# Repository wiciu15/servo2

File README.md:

# Servo 2
## 3-phase AC servomotor driver

This is a project of a servo inverter to drive 3-phase AC motor with/out encoder feedback

It's in alpha development so there are many bugs and things included in software but not really working/tested.

DEMO video: https://www.youtube.com/watch?v=Hu02lt5aCbM

CNC DEMO: https://www.youtube.com/watch?v=LXm4no8DIPE

This is a free software under the GNU license, you can redistribute it and/or modify it under the terms
of the GNU General Public License version 3 as published by the Free Software Foundation.
This project is shared with public for educational purposes, without WARRANTY and Author is not liable for any damages caused directly
or indirectly by this software/hardware. The board is mains-powered. High voltage can kill you. Have caution when using high voltage devices

## Features

- Manual voltage and frequency control
- U/f scalar motor control
- Open loop current control for test purposes
- Field-oriented vector control (FOC) for PMSM/BLDC motors with encoder feedback
- Encoders support:
  -  ABZ encoder with differential driver output, needs one manual rotation to index with a rotor properly
  -  Mitsubishi J2/J2s/J4/JE series, baud rate 2 500 000 bits/s, implementation is working but need some polish
  -  Tamagawa T-Format encoders - tested with ABB BSM-series motor, baud rate 2 500 000 bits/s, most robust implementation and testing at this moment
  -  Panasonic minas series encoder - support in early development, not much tested and buggy
  -  DELTA NH4 series T+ T- encoder - very early development
- Braking chopper control
- under/overvoltage, overcurrent, short-circuit and other errors detection and handling
- Communication with PC using MODBUS over USB-CDC
- simple CANopen node for fieldbus control
- Parameter set, with non-volatile storage in external EEPROM
- control and monitoring of drive using OLED screen and buttons
- ramp generators and limiters for current,speed and position control loops

## To-do in the future

- I2t thermal monitoring of motor
- sensorless rotor angle aquisition
- analog and digital I/O
- step/dir input
- current and speed loop gains auto-tuning
- motor parameters automatic measurement

## Used third-party software
- I2C EEPROM driver by ControllersTech
- OLED driver https://github.com/afiskon/stm32-ssd1306
- stModbus https://github.com/wiciu15/stModbus/
- CANopenNode https://github.com/CANopenNode/CANopenNode
- embedded printf implementation https://github.com/mpaland/printf
- FreeRTOS

## Hardware modification
MOdifications of rev.A of CPU board
- data/command line to OLED screen(PA15)
- bridge between tim1break input (PE15) and overcurrent interrupt(PA1)(break interrupt was not working i dont know why just bridged it to EXTI on other pin).
- OLED CLK is moved to PA5, PB3 is used as DEBUG_SWO.
- added filter to GND on FAULT line from power board to enchance noise rejection from EMI(i was getting random short-circuit errors).

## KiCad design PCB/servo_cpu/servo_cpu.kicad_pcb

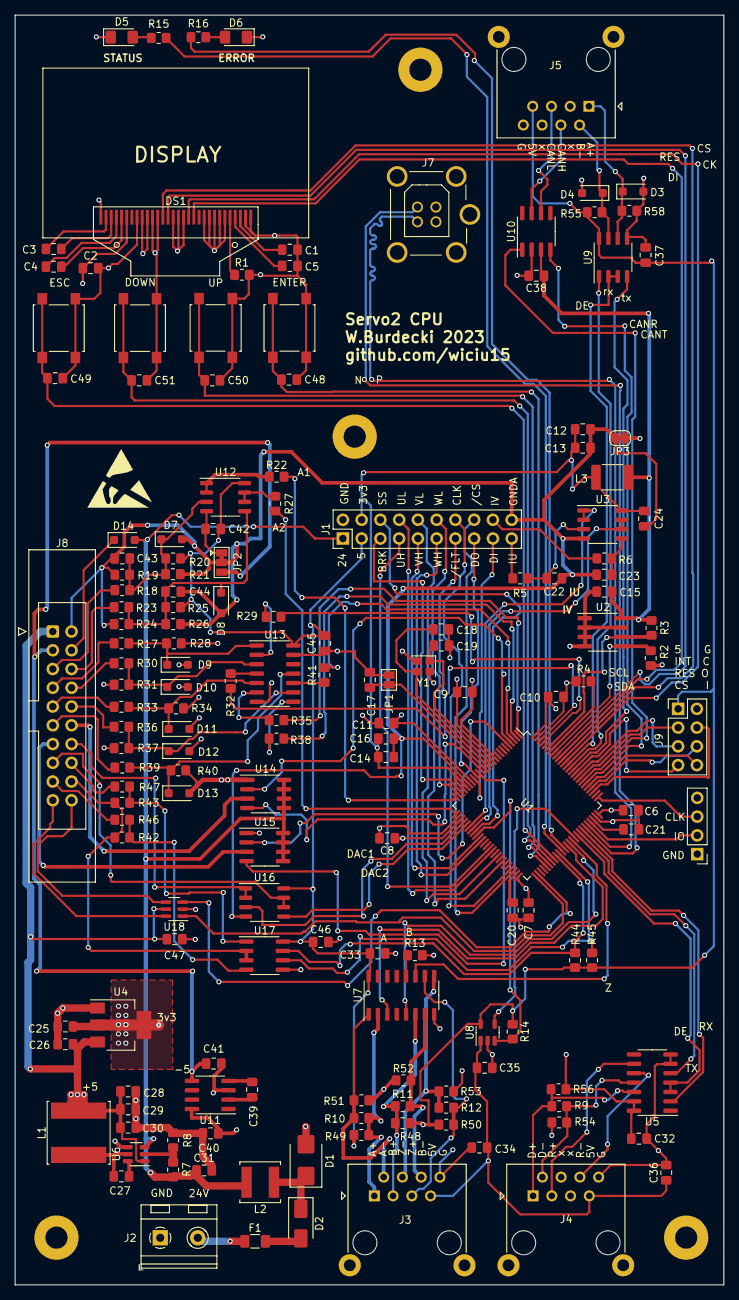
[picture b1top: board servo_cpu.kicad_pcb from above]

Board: 4 copper layers, 96.0 x 172.0 mm, 166 parts (0 on the bottom side), 151 nets.

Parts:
C1, C2, C3, C4, C5, C6, C7, C8, C9, C10, C11, C12, C13, C14, C15, C16, C20, C21, C24, C25, C26, C32, C33, C34, C35, C36, C37, C38, C40: 2u2; C_0805_2012Metric_Pad1.18x1.45mm_HandSolder
C17, C27, C42, C43, C44, C45, C46, C47, C48, C49, C50, C51: 100n; C_0805_2012Metric_Pad1.18x1.45mm_HandSolder
C18, C19: 12p; C_0805_2012Metric_Pad1.18x1.45mm_HandSolder
C22, C23: 1u; C_0805_2012Metric_Pad1.18x1.45mm_HandSolder
C28, C29, C30, C31, C39, C41: 22u; C_0805_2012Metric_Pad1.18x1.45mm_HandSolder
D1: SM6T27A; D_SMB
D2: US1B; D_SMA
D3, D4: BZT52B6v2; D_SOD-123F
D5: GREEN_LED; D_1206_3216Metric_Pad1.42x1.75mm_HandSolder
D6: RED_LED; D_1206_3216Metric_Pad1.42x1.75mm_HandSolder
D7, D8, D9, D10, D11, D12, D13: BZT52B5v1; D_SOD-123F
D14: 1N4148; D_SOD-123F
DS1: OLED-128O064D
F1: 615mA PTC; Fuse_1206_3216Metric
J1: PWR board; PinHeader_2x10_P2.54mm_Vertical
J2: Control power; TerminalBlock_RND_205-00232_1x02_P5.08mm_Horizontal
J3: ABZ; RJ45_Ninigi_GE
J4: Serial Encoder; RJ45_Ninigi_GE
J5: CONN; RJ45_Ninigi_GE
J6: DEBUG; PinHeader_1x04_P2.54mm_Vertical
J7: USB_B; USB
J8: I/O; IDC-Header_2x10_P2.54mm_Latch_Vertical
J9: EXT; PinHeader_2x04_P2.54mm_Vertical
JP1: RESET; SolderJumper-2_P1.3mm_Open_Pad1.0x1.5mm
JP2: OPA-V; SolderJumper-3_P1.3mm_Bridged12_Pad1.0x1.5mm
JP3: GND; SolderJumper-2_P1.3mm_Bridged_RoundedPad1.0x1.5mm
L1: 4u7; L_Sunlord_SWPA8040S
L2: 10u; L_Sunlord_SWPA5040S
L3: 470u; L_1812_4532Metric_Pad1.30x3.40mm_HandSolder
MH1, MH1#2, MH1#3, MH1#4: MountingHole_2.7mm_M2.5_DIN965_Pad
R1: 820k; R_0805_2012Metric_Pad1.20x1.40mm_HandSolder
R2, R3: 4,7k; R_0805_2012Metric_Pad1.20x1.40mm_HandSolder
R4, R15, R16, R44, R45, R55: 1k; R_0805_2012Metric_Pad1.20x1.40mm_HandSolder
R5, R6: 22R; R_0805_2012Metric_Pad1.20x1.40mm_HandSolder
R7: 220k; R_0805_2012Metric_Pad1.20x1.40mm_HandSolder
R8: 18k; R_0805_2012Metric_Pad1.20x1.40mm_HandSolder
R9, R22, R27: 150R; R_0805_2012Metric_Pad1.20x1.40mm_HandSolder
R10, R11, R12: 220R; R_0805_2012Metric_Pad1.20x1.40mm_HandSolder
R13, R14, R17, R18, R19, R23, R24, R29, R30, R32, R33, R35, R36, R38, R39, R41: 10k; R_0805_2012Metric_Pad1.20x1.40mm_HandSolder
R20, R21, R25, R26: 3k3; R_0805_2012Metric_Pad1.20x1.40mm_HandSolder
R28, R31, R34, R37, R40, R42, R43: 2k2; R_0805_2012Metric_Pad1.20x1.40mm_HandSolder
R46, R47, R48, R49, R50, R51, R52, R53, R54, R56, R58: 470R; R_0805_2012Metric_Pad1.20x1.40mm_HandSolder
SW1: ENTER; SW_SPST_B3S-1000
SW2: ESC; SW_SPST_B3S-1000
SW3: UP; SW_SPST_B3S-1000
SW4: DOWN; SW_SPST_B3S-1000
U1: STM32F407VETx; LQFP-100_14x14mm_P0.5mm
U2: M24C02-WMN; SOIC-8_3.9x4.9mm_P1.27mm
U3, U12, U16: TS912; SO-8_3.9x4.9mm_P1.27mm
U4: AP1117-33; SOT-223-3_TabPin2
U5: ISL83491; SO-14_3.9x8.65mm_P1.27mm
U6: AP63205WU; TSOT-23-6
U7: AM26LS32A; SO-16_3.9x9.9mm_P1.27mm
U8: AP2151A; SOT-23-5
U9: MAX485E; SO-8_3.9x4.9mm_P1.27mm
U10: SN65HVD232; SOIC-8_3.9x4.9mm_P1.27mm
U11: LMC7660; SOIC-8_3.9x4.9mm_P1.27mm
U13: 74HC14; SO-14_3.9x8.65mm_P1.27mm
U14, U15: ISP742RI; SOIC-8_3.9x4.9mm_P1.27mm
U17: VO0661T; SOIC-8_3.9x4.9mm_P1.27mm
U18: 74LVC2G04; SC-74-6_1.5x2.9mm_P0.95mm
Y1: 16M xt224; Crystal_SMD_2520-4Pin_2.5x2.0mm

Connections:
+3.3VA: C12.1, C13.1, C14.1, C16.1, C24.1, J1.19, L3.1, U1.21 (VREF+), U1.22 (VDDA), U3.8 (V+)
+3V3: C2.1, C6.1, C7.1, C8.1, C9.1, C10.1, C11.1, C15.1, C25.1, C32.1, C38.1, DS1.6 (VBAT), DS1.9 (VDD), DS1.10 (BS0), J6.4, L3.2, R2.1, R3.1, R56.1, U1.11 (VDD), U1.19 (VDD), U1.28 (VDD), U1.50 (VDD), U1.75 (VDD), U1.100 (VDD), U2.8 (VCC), U4.2 (VO), U5.13 (VCC), U5.14 (VCC), U10.3 (VCC)
+5V: C26.1, C28.1, C29.1, C30.1, C33.1, C37.1, C40.1, C42.1, C45.1, C46.1, C47.1, J1.2, J5.7, J8.1, J9.1, L1.2, R14.1, R20.2, R25.2, R44.2, R45.2, R48.1, R49.1, R50.1, R55.1, U4.3 (VI), U6.1 (FB), U7.16 (Vcc), U8.5 (IN), U9.8 (VCC), U11.8 (V+), U12.8 (V+), U13.14 (VCC), U16.8 (V+), U17.8 (VCC), U18.5 (VCC)
+5VL: C34.1, C35.1, C36.1, J3.7, J4.7, U8.1 (OUT)
+24V: C31.1, D14.2 (A), J1.1, L2.2, R7.1, U6.3 (IN), U14.5 (Vbb), U14.6 (Vbb), U14.7 (Vbb), U14.8 (Vbb), U15.5 (Vbb), U15.6 (Vbb), U15.7 (Vbb), U15.8 (Vbb)
-5V: C41.1, J8.3, JP2.3 (B), U11.5 (VOUT)
A: J3.1, R10.2, R49.2, U7.2 (1A)
A+: D3.1 (K), J5.1, R58.1, U9.6 (A)
ADC_CLK: J1.14, U1.47 (PB10)
ADC_CS: J1.13, U1.48 (PB11)
ADC_MISO: J1.8, U1.17 (PC2)
ADC_MOSI: J1.9, U1.18 (PC3)
AIN1: J8.5, R18.2
AIN1_ADC: R22.1, U1.25 (PA2)
AIN2: J8.6, R23.2
AIN2_ADC: R27.1, U1.26 (PA3)
AOUT1: J8.14, U16.1, U16.2 (-)
AOUT2: J8.15, U16.6 (-), U16.7
A_OUT: J8.19, U18.6
B: J3.3, R11.1, R48.2, U7.6 (2A)
B-: D4.1 (K), J5.2, R55.2, U9.7 (B)
BRAKE: J1.3, U1.23 (PA0)
BTN_DOWN: C51.1, SW4.1, U1.57 (PD10)
BTN_ENTER: C48.1, SW1.1, U1.55 (PD8)
BTN_ESC: C49.1, SW2.1, U1.58 (PD11)
BTN_UP: C50.1, SW3.1, U1.56 (PD9)
B_OUT: J8.20, U18.4
CANH: J5.4, U10.7 (CANH)
CANL: J5.5, U10.6 (CANL)
CAN_RX: U1.81 (PD0), U10.4 (R)
CAN_TX: U1.82 (PD1), U10.1 (D)
DAC1: U1.29 (PA4), U16.3 (+)
DAC2: U1.30 (PA5), U16.5 (+)
DEBUG_CLK: J6.3, U1.76 (PA14)
DEBUG_IO: J6.2, U1.72 (PA13)
DIN1: J8.7, R17.2
DIN1_CPU: R29.2, U1.97 (PE0)
DIN2: J8.8, R30.2
DIN2_CPU: R32.2, U1.98 (PE1)
DIN3: J8.9, R33.2
DIN3_CPU: R35.2, U1.1 (PE2)
DIN4: J8.10, R36.2
DIN4_CPU: R38.2, U1.2 (PE3)
DIN5: J8.11, R39.2
DIN5_CPU: R41.2, U1.3 (PE4)
DISPLAY_CLK: DS1.18 (D0), U1.89 (PB3)
DISPLAY_MOSI: DS1.19 (D1), U1.91 (PB5)
DOUT1: J8.12, U14.3 (OUT)
DOUT1_CPU: U1.4 (PE5), U14.2 (IN)
DOUT1_STATUS: U1.15 (PC0), U14.4 (ST)
DOUT2: J8.13, U15.3 (OUT)
DOUT2_CPU: U1.5 (PE6), U15.2 (IN)
DOUT2_STATUS: U1.16 (PC1), U15.4 (ST)
EEPROM_SCL: R3.2, U1.95 (PB8), U2.6 (SCL)
EEPROM_SDA: R2.2, U1.93 (PB7), U2.5 (SDA)
ENCODER_DE: U1.67 (PA8), U5.3 (~RE), U5.4 (DE)
ENCODER_ENABLE: U1.66 (PC9), U8.4 (EN)
ENCODER_RX: U1.69 (PA10), U5.2 (RO)
ENCODER_TX: U1.68 (PA9), U5.5 (DI)
ENC_A: U1.63 (PC6), U7.3 (1Y)
ENC_A_OUT_CPU: U1.51 (PB12), U18.1
ENC_B: U1.64 (PC7), U7.5 (2Y)
ENC_B_OUT_CPU: U1.52 (PB13), U18.3
ENC_Z: U1.65 (PC8), U7.11 (3Y)
EXT_CLK: J9.4, U1.78 (PC10)
EXT_CS: J9.7, U1.85 (PD4)
EXT_INT: J9.3, U1.83 (PD2)
EXT_MISO: J9.6, U1.79 (PC11)
EXT_MOSI: J9.8, U1.80 (PC12)
EXT_RESET: J9.5, U1.84 (PD3)
GND: C1.2, C2.2, C5.2, C6.2, C7.2, C8.2, C9.2, C10.2, C11.2, C15.2, C17.2, C18.2, C19.2, C20.2, C21.2, C25.2, C26.2, C28.2, C29.2, C30.2, C31.2, C32.2, C33.2, C34.2, C35.2, C36.2, C37.2, C38.2, C40.2, C41.2, C45.2, C46.2, C47.2, C48.2, C49.2, C50.2, C51.2, D1.2 (A2), D3.2 (A), D4.2 (A), D5.1 (K), D6.1 (K), D9.2 (A), D10.2 (A), D11.2 (A), D12.2 (A), D13.2 (A), DS1.1 (GND), DS1.8 (VSS), DS1.11 (BS1), DS1.12 (BS2), DS1.15 (D/~C), DS1.16 (R/~W), DS1.17 (E/~RD), DS1.21 (D3), DS1.22 (D4), DS1.23 (D5), DS1.24 (D6), DS1.25 (D7), DS1.29 (VLSS), DS1.30 (GND), J1.20, J2.1, J3.8, J3.SH, J4.8, J4.SH, J5.8, J5.SH, J6.1, J7.4 (GND), J7.5 (Shield), J9.2, JP1.1 (A), JP3.1 (A), MH1.1, MH1#2.1, MH1#3.1, MH1#4.1, R1.2, R4.1, R8.2, R13.2, R28.1, R31.1, R34.1, R37.1, R40.1, R51.2, R52.2, R53.2, R54.2, R58.2, SW1.2, SW2.2, SW3.2, SW4.2, U1.10 (VSS), U1.27 (VSS), U1.74 (VSS), U1.99 (VSS), U2.1 (E0), U2.2 (E1), U2.3 (E2), U2.4 (VSS), U2.7 (~WC), U4.1 (GND), U5.6 (GND), U5.7 (GND), U6.4 (GND), U7.8 (GND), U8.2 (GND), U9.5 (GND), U10.2 (GND), U11.3 (GND), U13.7 (GND), U13.13, U14.1 (GND), U15.1 (GND), U17.5 (GND), U18.2 (GND), Y1.2, Y1.4
GNDA: C12.2, C13.2, C14.2, C16.2, C22.2, C23.2, C24.2, C43.2, C44.2, D7.2 (A), D8.2 (A), J1.11, J8.2, JP2.2 (C), JP3.2 (B), R19.1, R21.1, R24.1, R26.1, U1.20 (VSSA), U3.4 (V-), U16.4 (V-)
IGBT_fault: J1.7, U1.24 (PA1)
I_U: J1.10, R5.2
I_V: J1.12, R6.2
LED_ERROR: R16.1, U1.62 (PD15)
LED_STATUS: R15.1, U1.61 (PD14)
MD: J4.1, R9.1, R56.2, U5.12 (A)
MDR: J4.2, R9.2, R54.1, U5.11 (~B)
MODBUS_DE: U1.88 (PD7), U9.2 (~RE), U9.3 (DE)
MODBUS_RX: U1.87 (PD6), U9.1 (RO)
MODBUS_TX: U1.86 (PD5), U9.4 (DI)
MR: J4.3, U5.9 (Y)
MRR: J4.6, U5.10 (~Z)
unnamed: D1.1 (A1), D2.1 (K), L2.1
unnamed: D2.2 (A), F1.2
unnamed: D5.2 (A), R15.2
unnamed: D6.2 (A), R16.2
unnamed: C43.1, D7.1 (K), R18.1, R19.2, R20.1, R21.2, U12.3 (+)
unnamed: C44.1, D8.1 (K), R23.1, R24.2, R25.1, R26.2, U12.5 (+)
unnamed: D9.1 (K), R17.1, R28.2, U13.1
unnamed: D10.1 (K), R30.1, R31.2, U13.3
unnamed: D11.1 (K), R33.1, R34.2, U13.5
unnamed: D12.1 (K), R36.1, R37.2, U13.9
unnamed: D13.1 (K), R39.1, R40.2, U13.11
unnamed: D14.1 (K), J8.4
unnamed: C4.2, DS1.5 (C1N)
unnamed: C4.1, DS1.4 (C1P)
unnamed: C3.1, DS1.2 (C2N)
unnamed: C3.2, DS1.3 (C2P)
unnamed: DS1.26 (IREF), R1.1
unnamed: C1.1, DS1.28 (VCC)
unnamed: C5.1, DS1.27 (VCOMH)
unnamed: F1.1, J2.2
unnamed: C17.1, JP1.2 (B), U1.14 (NRST)
unnamed: C42.2, JP2.1 (A), U12.4 (V-)
unnamed: R29.1, U13.2
unnamed: R32.1, U13.4
unnamed: R35.1, U13.6
unnamed: R38.1, U13.8
unnamed: R41.1, U13.10
unnamed: R4.2, U1.94 (BOOT0)
unnamed: U1.31 (PA6), U3.1, U3.2 (-)
unnamed: U1.32 (PA7), U3.6 (-), U3.7
unnamed: C19.1, U1.12 (PH0), Y1.1
unnamed: C18.1, U1.13 (PH1), Y1.3
unnamed: C20.1, U1.49 (VCAP_1)
unnamed: C21.1, U1.73 (VCAP_2)
unnamed: C22.1, R5.1, U3.3 (+)
unnamed: C23.1, R6.1, U3.5 (+)
unnamed: C27.2, U6.6 (BST)
unnamed: R7.2, R8.1, U6.2 (EN)
unnamed: C27.1, L1.1, U6.5 (SW)
unnamed: R13.1, U7.12 (/G)
unnamed: C39.1, U11.2 (CAP+)
unnamed: C39.2, U11.4 (CAP-)
unnamed: R22.2, U12.1, U12.2 (-)
unnamed: R27.2, U12.6 (-), U12.7
unnamed: R43.2, R47.2, U17.1 (A1)
unnamed: R42.1, R46.2, U17.4 (A2)
PWMU_H: J1.4, U1.39 (PE8)
PWMU_L: J1.17, U1.40 (PE9)
PWMV_H: J1.5, U1.35 (PB0)
PWMV_L: J1.16, U1.42 (PE11)
PWMW_H: J1.6, U1.36 (PB1)
PWMW_L: J1.15, U1.44 (PE13)
SOFTSTART: J1.18, U1.33 (PC4)
STEP_COMM: J8.18, R42.2, R43.1, U17.2 (C1), U17.3 (C2)
STEP_F: J8.16, R47.1
STEP_F_CPU: R44.1, U1.59 (PD12), U17.7 (VO1)
STEP_R: J8.17, R46.1
STEP_R_CPU: R45.1, U1.60 (PD13), U17.6 (VO2)
USB_N: J7.2 (D-), U1.70 (PA11)
USB_P: J7.3 (D+), U1.71 (PA12)
Z: J3.5, R12.1, R50.2, U7.10 (3A)
/A: J3.2, R10.1, R51.1, U7.1 (1B)
/B: J3.6, R11.2, R52.1, U7.7 (2B)
/DISPLAY_CS: DS1.13 (~CS), U1.90 (PB4)
/DISPLAY_RESET: DS1.14 (~RES), U1.92 (PB6)
/ENCODER_SHORT: R14.2, U1.34 (PC5), U8.3 (~FLG)
/Z: J3.4, R12.2, R53.1, U7.9 (3B)

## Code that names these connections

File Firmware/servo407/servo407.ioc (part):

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Mcu.Name=STM32F407V(E-G)Tx
Mcu.Package=LQFP100
Mcu.UserName=STM32F407VETx
PA0-WKUP.GPIOParameters=GPIO_Label
PA0-WKUP.GPIO_Label=BRAKE
PA0-WKUP.Signal=S_TIM2_CH1_ETR
PA1.GPIOParameters=GPIO_Label
PA1.GPIO_Label=IGBT_FAULT
PA1.Signal=GPXTI1
PA10.GPIOParameters=GPIO_Label
PA10.GPIO_Label=ENCODER_RX
PA10.Mode=Asynchronous
PA10.Signal=USART1_RX
PA11.Mode=Device_Only
PA11.Signal=USB_OTG_FS_DM
PA12.Mode=Device_Only
PA12.Signal=USB_OTG_FS_DP
PA13.Mode=Trace_Asynchronous_SW
PA13.Signal=SYS_JTMS-SWDIO
PA14.Mode=Trace_Asynchronous_SW
PA14.Signal=SYS_JTCK-SWCLK
PA15.GPIOParameters=GPIO_Label
PA15.GPIO_Label=OLED_DC
PA15.Signal=GPIO_Output
PA2.Signal=ADCx_IN2
PA3.Signal=ADCx_IN3
PA4.GPIOParameters=GPIO_Label
PA4.GPIO_Label=DAC1
PA4.Signal=COMP_DAC1_group
PA5.GPIOParameters=GPIO_Label
PA5.GPIO_Label=OLED_CLK
PA5.Mode=TX_Only_Simplex_Unidirect_Master
PA5.Signal=SPI1_SCK
PA6.GPIOParameters=GPIO_Label
PA6.GPIO_Label=I_U
PA6.Signal=ADCx_IN6
PA7.GPIOParameters=GPIO_Label
PA7.GPIO_Label=I_V
PA7.Signal=ADCx_IN7
PA8.GPIOParameters=PinState,GPIO_Label
PA8.GPIO_Label=ENCODER_DE
PA8.PinState=GPIO_PIN_RESET
PA8.Signal=GPIO_Output
PA9.GPIOParameters=GPIO_Label
PA9.GPIO_Label=ENCODER_TX
PA9.Mode=Asynchronous
PA9.Signal=USART1_TX
PB0.GPIOParameters=GPIO_ModeDefaultPP,GPIO_Speed,GPIO_PuPd
PB0.GPIO_ModeDefaultPP=GPIO_MODE_AF_PP
PB0.GPIO_PuPd=GPIO_NOPULL
PB0.GPIO_Speed=GPIO_SPEED_FREQ_LOW
PB0.Mode=PWM Generation2 CH2 CH2N
PB0.Signal=TIM1_CH2N
PB1.GPIOParameters=GPIO_ModeDefaultPP,GPIO_Speed,GPIO_PuPd
PB1.GPIO_ModeDefaultPP=GPIO_MODE_AF_PP
PB1.GPIO_PuPd=GPIO_NOPULL
PB1.GPIO_Speed=GPIO_SPEED_FREQ_LOW
PB1.Mode=PWM Generation3 CH3 CH3N
PB1.Signal=TIM1_CH3N
PB10.GPIOParameters=GPIO_Label
PB10.GPIO_Label=ADC_CLK
PB10.Mode=Full_Duplex_Master
PB10.Signal=SPI2_SCK
PB11.GPIOParameters=PinState,GPIO_Label
PB11.GPIO_Label=ADC_CS
PB11.PinState=GPIO_PIN_SET
PB11.Signal=GPIO_Output
PB3.Mode=Trace_Asynchronous_SW
PB3.Signal=SYS_JTDO-SWO
PB4.GPIOParameters=PinState,GPIO_Label
PB4.GPIO_Label=OLED_CS
PB4.PinState=GPIO_PIN_SET
PB4.Signal=GPIO_Output
PB5.GPIOParameters=GPIO_Label
PB5.GPIO_Label=OLED_MOSI
PB5.Mode=TX_Only_Simplex_Unidirect_Master
PB5.Signal=SPI1_MOSI
PB6.GPIOParameters=PinState,GPIO_Label
PB6.GPIO_Label=OLED_RESET
PB6.PinState=GPIO_PIN_SET
PB6.Signal=GPIO_Output
PB7.GPIOParameters=GPIO_Label
PB7.GPIO_Label=EEPROM_SDA
PB7.Mode=I2C
PB7.Signal=I2C1_SDA
PB8.GPIOParameters=GPIO_Label
PB8.GPIO_Label=EEPROM_SCL
PB8.Mode=I2C
PB8.Signal=I2C1_SCL
PB9.GPIOParameters=PinState,GPIO_Label
PB9.GPIO_Label=MODBUS_DE
PB9.PinState=GPIO_PIN_SET
PB9.Signal=GPIO_Output
PC10.Mode=Full_Duplex_Master
PC10.Signal=SPI3_SCK
PC11.Mode=Full_Duplex_Master
PC11.Signal=SPI3_MISO
PC12.Mode=Full_Duplex_Master
PC12.Signal=SPI3_MOSI
PC2.GPIOParameters=GPIO_Label
PC2.GPIO_Label=ADC_MISO
PC2.Mode=Full_Duplex_Master
PC2.Signal=SPI2_MISO
PC3.GPIOParameters=GPIO_Label
PC3.GPIO_Label=ADC_MOSI
PC3.Mode=Full_Duplex_Master
PC3.Signal=SPI2_MOSI
PC4.GPIOParameters=GPIO_Label
PC4.GPIO_Label=SOFTSTART
PC4.Signal=GPIO_Output
PC5.GPIOParameters=GPIO_Label
PC5.GPIO_Label=ENC_SHORT
PC5.Signal=GPXTI5
PC6.GPIOParameters=GPIO_Label
PC6.GPIO_Label=ENC_A
PC6.Signal=S_TIM3_CH1
PC7.GPIOParameters=GPIO_Label
PC7.GPIO_Label=ENC_B
PC7.Signal=S_TIM3_CH2
PC8.GPIOParameters=GPIO_Label
PC8.GPIO_Label=ENC_Z
PC8.Signal=GPXTI8
PC9.GPIOParameters=GPIO_Label
PC9.GPIO_Label=ENC_ENABLE
PC9.Signal=GPIO_Output
PD0.Mode=CAN_Activate
PD0.Signal=CAN1_RX
PD1.Mode=CAN_Activate
PD1.Signal=CAN1_TX
PD10.GPIOParameters=GPIO_PuPd,GPIO_Label
PD10.GPIO_Label=BTN_DOWN
PD10.GPIO_PuPd=GPIO_PULLUP
PD10.Signal=GPIO_Input
PD11.GPIOParameters=GPIO_PuPd,GPIO_Label
PD11.GPIO_Label=BTN_BACK
PD11.GPIO_PuPd=GPIO_PULLUP
PD11.Signal=GPIO_Input
PD12.GPIOParameters=GPIO_Label
PD12.GPIO_Label=STEP_IN
PD12.Signal=S_TIM4_CH1
PD13.GPIOParameters=GPIO_Label,GPIO_ModeDefaultEXTI
PD13.GPIO_Label=DIR_IN
PD13.GPIO_ModeDefaultEXTI=GPIO_MODE_IT_RISING_FALLING
PD13.Signal=GPXTI13
PD14.GPIOParameters=PinState,GPIO_Label
PD14.GPIO_Label=LED_STATUS
PD14.PinState=GPIO_PIN_SET
PD14.Signal=GPIO_Output
PD15.GPIOParameters=PinState,GPIO_Label
PD15.GPIO_Label=LED_ERROR
PD15.PinState=GPIO_PIN_SET
PD15.Signal=GPIO_Output
PD2.GPIOParameters=GPIO_Label
PD2.GPIO_Label=ETH_INT
PD2.Signal=GPXTI2
PD3.GPIOParameters=GPIO_Label
PD3.GPIO_Label=ETH_RESET
PD3.Signal=GPIO_Output
PD4.GPIOParameters=PinState,GPIO_Label
PD4.GPIO_Label=ETH_CS
PD4.PinState=GPIO_PIN_SET
PD4.Signal=GPIO_Output
PD5.GPIOParameters=GPIO_Label
PD5.GPIO_Label=MODBUS_TX
PD5.Mode=Asynchronous
PD5.Signal=USART2_TX
PD6.GPIOParameters=GPIO_Label
PD6.GPIO_Label=MODBUS_RX
PD6.Mode=Asynchronous
PD6.Signal=USART2_RX
PD7.GPIOParameters=GPIO_Label
PD7.GPIO_Label=MODBUS_DE
PD7.Signal=GPIO_Output
PD8.GPIOParameters=GPIO_PuPd,GPIO_Label
PD8.GPIO_Label=BTN_ENT
PD8.GPIO_PuPd=GPIO_PULLUP
PD8.Signal=GPIO_Input
PD9.GPIOParameters=GPIO_PuPd,GPIO_Label
PD9.GPIO_Label=BTN_UP
PD9.GPIO_PuPd=GPIO_PULLUP
PD9.Signal=GPIO_Input
PE0.GPIOParameters=GPIO_Label
PE0.GPIO_Label=DIN1
PE0.Signal=GPIO_Input
PE1.GPIOParameters=GPIO_Label
PE1.GPIO_Label=DIN2
PE1.Signal=GPIO_Input
PE11.GPIOParameters=GPIO_ModeDefaultPP,GPIO_Speed,GPIO_PuPd
PE11.GPIO_ModeDefaultPP=GPIO_MODE_AF_PP
PE11.GPIO_PuPd=GPIO_NOPULL
PE11.GPIO_Speed=GPIO_SPEED_FREQ_LOW
PE11.Signal=S_TIM1_CH2
PE13.GPIOParameters=GPIO_ModeDefaultPP,GPIO_Speed,GPIO_PuPd
PE13.GPIO_ModeDefaultPP=GPIO_MODE_AF_PP
PE13.GPIO_PuPd=GPIO_NOPULL
PE13.GPIO_Speed=GPIO_SPEED_FREQ_LOW
PE13.Signal=S_TIM1_CH3
PE15.Mode=Activate-Break-Input
PE15.Signal=TIM1_BKIN
PE2.GPIOParameters=GPIO_Label
PE2.GPIO_Label=DIN3
PE2.Signal=GPIO_Input
PE3.GPIOParameters=GPIO_Label
PE3.GPIO_Label=DIN4
PE3.Signal=GPIO_Input
PE4.GPIOParameters=GPIO_Label
PE4.GPIO_Label=DIN5
PE4.Signal=GPIO_Input
PE5.GPIOParameters=GPIO_Label
PE5.GPIO_Label=DOUT1
PE5.Signal=GPIO_Output
PE6.GPIOParameters=GPIO_Label
PE6.GPIO_Label=DOUT2
PE6.Signal=GPIO_Output
PE8.GPIOParameters=GPIO_ModeDefaultPP,GPIO_Speed,GPIO_PuPd
PE8.GPIO_ModeDefaultPP=GPIO_MODE_AF_PP
PE8.GPIO_PuPd=GPIO_NOPULL
PE8.GPIO_Speed=GPIO_SPEED_FREQ_LOW
PE8.Mode=PWM Generation1 CH1 CH1N
PE8.Signal=TIM1_CH1N
PE9.GPIOParameters=GPIO_ModeDefaultPP,GPIO_Speed,GPIO_PuPd
PE9.GPIO_ModeDefaultPP=GPIO_MODE_AF_PP
PE9.GPIO_PuPd=GPIO_NOPULL
PE9.GPIO_Speed=GPIO_SPEED_FREQ_LOW
PE9.Signal=S_TIM1_CH1
PH0-OSC_IN.Mode=HSE-External-Oscillator
PH0-OSC_IN.Signal=RCC_OSC_IN
PH1-OSC_OUT.Mode=HSE-External-Oscillator
PH1-OSC_OUT.Signal=RCC_OSC_OUT
RCC.HSE_VALUE=16000000
RCC.SYSCLKFreq_VALUE=168000000
RCC.SYSCLKSource=RCC_SYSCLKSOURCE_PLLCLK
board=custom

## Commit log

2023-01-19 folder change
2023-01-19 pcb layout
2023-01-21 pcb work
2023-02-22 pcb routing
2023-02-27 cpu board
2023-02-27 cpu pcb
2023-02-28 cpu schematic
2023-03-06 CPU schematic done
2023-03-09 cpu pcb layout
2023-03-10 cpu pcb routing
2023-03-10 cpu board done
2023-03-22 inverter output voltage synthesis WIP
2023-04-17 output voltage synthesis is progress
2023-04-18 HOT ADC communication
2023-04-18 pwm modulation WIP
2023-05-25 modbus over USB CDC implemented
2023-06-05 manual and u/f control implemented
2023-06-06 open loop vector control implemented
2023-06-07 foc and mitsubishi encoder implemented
2023-06-07 fixed bug in hot adc, disabled mitsubishi encoder
    disabled mitsubishi encoder because it was not working and also causing issues with SPI2 DMA for hot adc
2023-06-08 hot adc fixed
    mitsubishi sometimes does not initialize
2023-06-08 mitsubishi encoder and speed limiter
2023-06-11 abz encoder implemented
2023-06-21 modbus usb rework and softstart delay added
2023-06-21 led status reporting implemented
2023-06-21 display library
2023-06-23 user interface implemented
2023-06-29 mitsubishi encoder resolution change
2023-06-29 svpwm implementation
2023-06-30 abz encoder polarity switch added
2023-07-05 panasonic minas encoder support
2023-07-05 panasonic rotation direction changed
2023-07-07 eeprom
2023-07-11 parameter saving by other eeprom library implemented
2023-07-13 braking chopper control implemented
2023-07-14 eeprom checksum check implemented
2023-07-23 tamagawa encoder slight rework
2023-07-25 fix for mitsubishi j2 encoders
    j2 encoder doesnt work over 5kHz
2023-07-25 current measurement noise filtered
2023-07-26 delta encoder in progress
2023-07-30 limiters and default parameters updated
2023-08-01 menu first implemented
2023-08-02 menu actions and monitor implementation
2023-08-03 menu monitor implemented
2023-08-03 current controller tuning
2023-09-20 CMSIS-DSP library implemented
2023-09-21 motor control loop execution speed optimized
2023-09-23 tamagawa encoder bugfix
2023-09-27 new parameter list progress
2023-10-06 new control modes implemented
2023-10-07 Revert "new control modes implemented"
    This reverts commit 8d178d27cb936a9ae3871c2e015a36b752bb5537.
2023-10-23 new parameter list progress status word added
2023-10-26 modbus with new parameter list
2023-10-31 new parameter set implemented
2023-11-02 speed ramp generator fixed
2023-11-02 Revert "Merge branch 'main' into new-parameter-set"
    This reverts commit baf1e8bbb4a0091322eba564e62bccc52cc87168, reversing
    changes made to 4cd528f12005d2d23f4941173ab873df024b014f.
2023-11-04 Tamagawa encoder direction flip
2023-11-16 simple position loop implemented
2023-11-29 output voltage compensation improved
2023-12-27 current controller performance improved
2023-12-27 profile trajectory generator
2023-12-28 add acceleration ctrl to position profile gen
2024-01-05 step/dir input added
2024-01-15 fixed motor noise when heavy reading from USB
2024-01-31 canopen node implemented
2024-02-01 canopen object dictionary WIP
2024-02-05 can parameter list reading WIP
2024-02-10 CAN object dictionary WIP
2024-02-23 switched oled_ck pin for swo debug option on DAC2
2024-02-26 CANbus control working in pp and pv modes
2024-10-18 abz encoder bugfix
2024-11-07 abz encoder debugged and improved
2024-11-08 mitsubishi encoder variable comm frequency added
2025-04-01 output voltage calculation bugfix
2025-04-07 delta encoder added acceleration detection
2025-04-07 delta encoder acceleration error trip
2025-06-05 tamagawa encoder response decoding
2025-07-22 omnuc g encoder support prototype
